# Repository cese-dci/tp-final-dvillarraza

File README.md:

## Trabajo práctico final de la asignatura DCI ##
Este repositorio contiene el trabajo práctico final para la asignatura de Diseño de Circuitos Impresos de la carrera de posgrado de FIUBA.

* Autor: Diego Villarraza
* Título corto del trabajo:  Replica detector de NH3
* Descripción:  El trabajo consiste en reazliar una replica del modulo "Ammonia Click" modelo MIKROE-4151 que desarrollo y comercializa la empresa Mikroe.
 El modulo es un detector de amoniaco (NH3) basado en el sensor MQ-137 para medir concentraciones en el rango de 5 a 200 ppm, concentraciones por encima
 de los 50 ppm pueden provocar graves trastornos de salud en el cuerpo humano.
 
## Licencia de este trabajo ##
GPL

## Estructura del TP FINAL ##

* doc: 
  * Notas de ingeniería propias.
  * Notas de aplicación propias.
  * Estudios previos, estado del arte, resumen de las investigaciones.
  * Notas con cálculos.
  * Dibujos adicionales.
  * Fotos de los prototipos.
  * Presupuestos, cotizaciones.
* info: 
  * Hojas de datos.
  * Notas de aplicación.
  * Info de productos comerciales.
  * Info en internet.
* pcb: Archivos de diseño esquemático y pcb.

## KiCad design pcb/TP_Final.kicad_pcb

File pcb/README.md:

## Archivos Kicad ##

* Archivos de proyecto.
* Esquemático.
* PCB.
* Modelos  3D.
* Bibliotecas de símbolos y huellas externas.

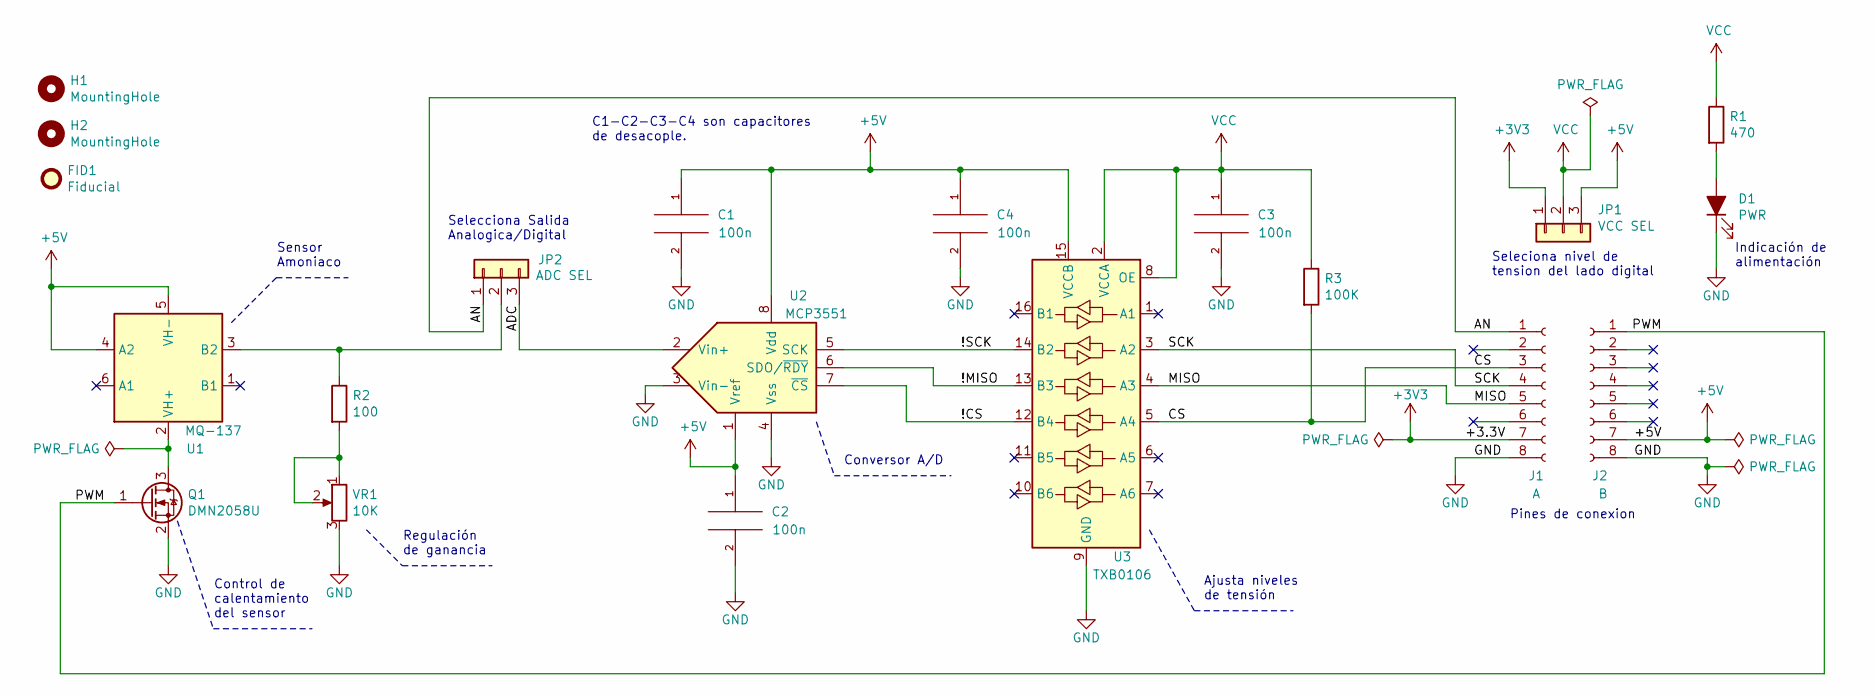
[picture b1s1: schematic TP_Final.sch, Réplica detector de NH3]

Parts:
C1, C2, C3, C4: 100n; C_0805_2012Metric
D1: PWR; LED_0805_2012Metric
FID1: Fiducial; Fiducial_0.75mm_Mask1.5mm
H1, H2: MountingHole; MountingHole_2.1mm
J1: A; PinHeader_1x08_P2.54mm_Vertical
J2: B; PinHeader_1x08_P2.54mm_Vertical
JP1: VCC SEL; PinHeader_1x03_P2.00mm_Vertical_SMD_Pin1Right
JP2: ADC SEL; PinHeader_1x03_P2.00mm_Vertical_SMD_Pin1Right
Q1: DMN2058U; SOT-23
R1: 470; R_0805_2012Metric
R2: 100; R_0805_2012Metric
R3: 100K; R_0805_2012Metric
U1: MQ-137; MQ-6
U2: MCP3551; SOIC-8_3.9x4.9mm_P1.27mm
U3: TXB0106; TSSOP-16_4.4x5mm_P0.65mm
VR1: 10K; Potentiometer_Bourns_3339H_Vertical

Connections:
+3V3: J1.7, JP1.1
+5V: C1.1, C2.1, C4.1, J2.7, JP1.3, U1.4 (A2), U1.5 (VH-), U2.1 (Vref), U2.8 (Vdd), U3.15 (VCCB)
/!CS: U2.7 (~CS~), U3.12 (B4)
/!MISO: U2.6 (SDO/~RDY~), U3.13 (B3)
/!SCK: U2.5 (SCK), U3.14 (B2)
/ADC: JP2.3, U2.2 (Vin+)
/AN: J1.1, JP2.1
/CS: J1.3, R3.2, U3.5 (A4)
/MISO: J1.5, U3.4 (A3)
/PWM: J2.1, Q1.1 (G)
/SCK: J1.4, U3.3 (A2)
GND: C1.2, C2.2, C3.2, C4.2, D1.1 (K), J1.8, J2.8, Q1.2 (S), U2.3 (Vin-), U2.4 (Vss), U3.9 (GND), VR1.3
unnamed: D1.2 (A), R1.2
unnamed: JP2.2, R2.1, U1.3 (B2)
unnamed: Q1.3 (D), U1.2 (VH+)
unnamed: R2.2, VR1.1, VR1.2
VCC: C3.1, JP1.2, R1.1, R3.1, U3.2 (VCCA), U3.8 (OE)

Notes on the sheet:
Sensor Amoniaco
C1-C2-C3-C4 son capacitores de desacople.
Indicación de alimentación
Regulación de ganancia
Selecciona Salida Analogica/Digital
Seleciona nivel de tension del lado digital
Pines de conexion
Conversor A/D
Control de calentamiento del sensor
Ajusta niveles de tensión

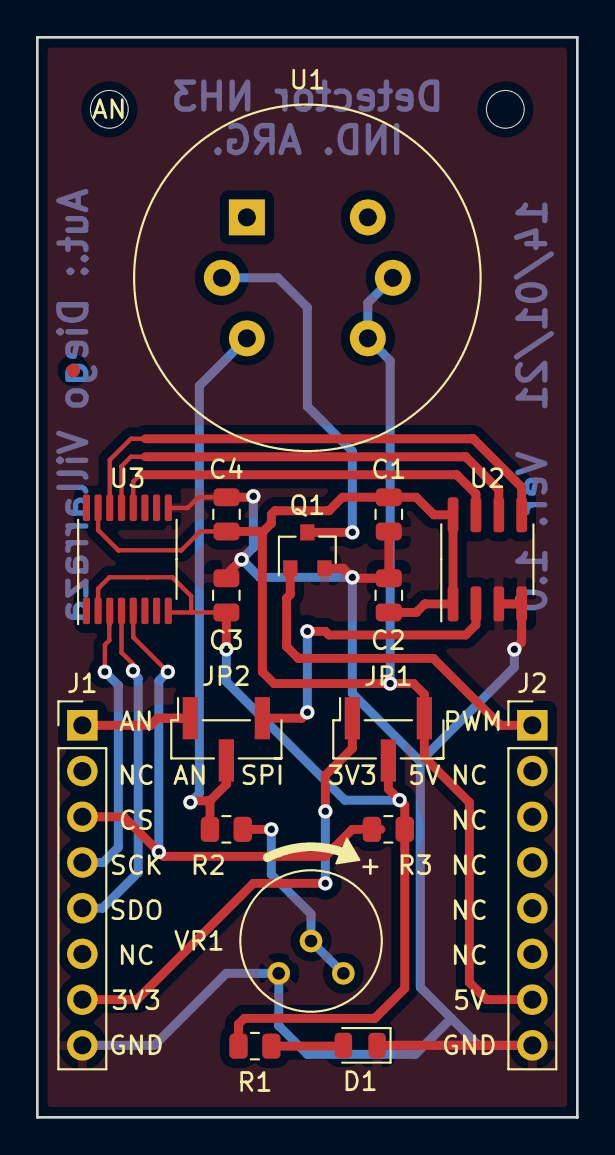
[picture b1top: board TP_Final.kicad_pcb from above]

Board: 2 copper layers, 30.0 x 60.0 mm, 20 parts (0 on the bottom side), 17 nets.

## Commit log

2021-08-30 Agrego esquemático propuesto
2021-08-30 Add files via upload
    Agrego fotos de PCB propuesto
2021-09-18 Actualizo README.md
2021-09-18 Agrego hojas de datos
2021-09-18 Agrego proyecto de kicad
2021-09-22 Actualizo esquematico
2021-09-23 Inicio PCB - Posicionamiento de componentes
2021-10-07 Actualizo PCB
2021-10-13 Version Final PCB

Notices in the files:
pcb/TP_Final.kicad_pcb:
Licencia: GPL
